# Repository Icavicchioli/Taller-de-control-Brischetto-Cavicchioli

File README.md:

tp1: https://www.overleaf.com/3525453746jbmzhwpqxbmw#78765e

tp2: https://www.overleaf.com/read/swpkgmxtgczf#749885

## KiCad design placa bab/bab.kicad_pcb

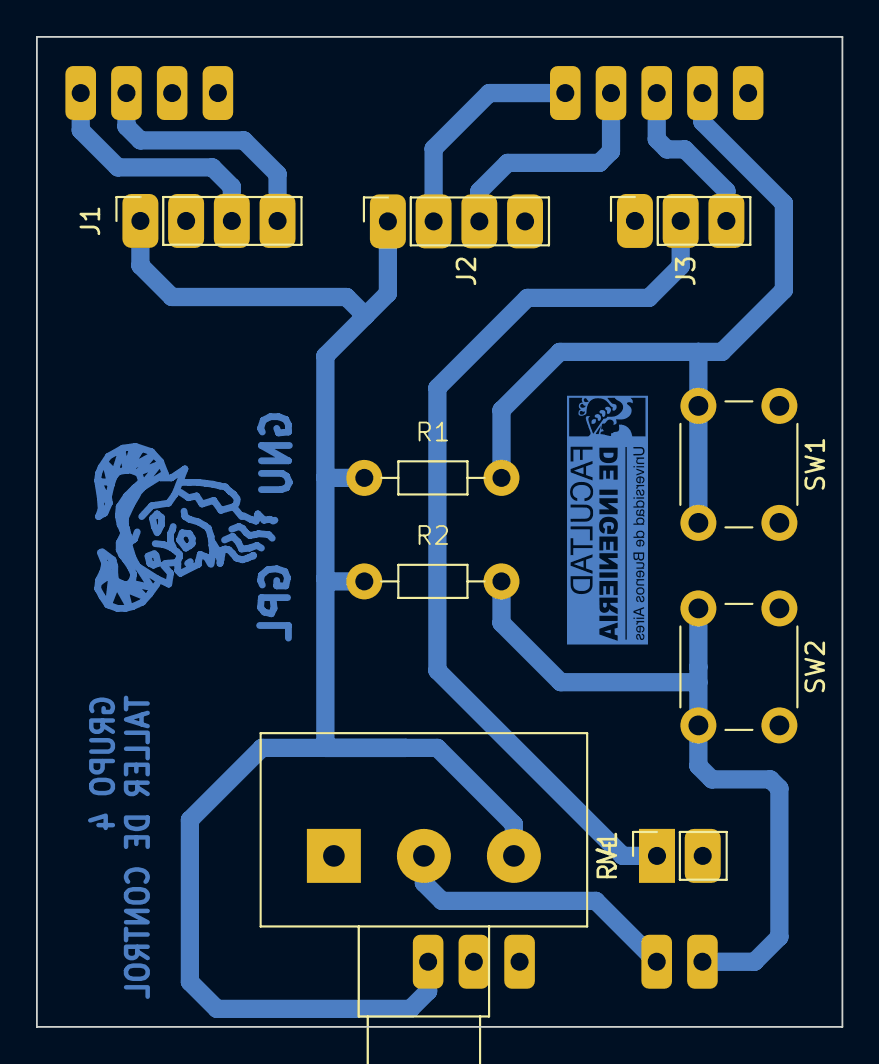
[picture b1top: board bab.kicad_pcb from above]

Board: 2 copper layers, 44.7 x 55.0 mm, 10 parts (1 on the bottom side), 11 nets.

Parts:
A1: Arduino_UNO_R3
J1: IMU; PinSocket_1x04_P2.54mm_Vertical
J2: HC05; PinSocket_1x04_P2.54mm_Vertical
J3: motor; PinSocket_1x03_P2.54mm_Vertical
J4: Alimentacion; PinSocket_1x02_P2.54mm_Vertical
R1, R2: 4K7; Resistencia THT
RV1: R_Potentiometer; Potentiometer_Alps_RK163_Single_Horizontal
SW1, SW2: SW_Push; SW_PUSH_6mm_H5mm

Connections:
+5V: A1.5 (+5V), J1.1, J2.1, R1.1, R2.1, RV1.3
/5v_ext: J3.2, J4.1
BTN1: A1.19 (D4), R1.2, SW1.2
BTN2: A1.10 (A1), R2.2, SW2.2
ECHO: A1.21 (D6), J2.3
GND: A1.6 (GND), A1.7 (GND), A1.29 (GND), J1.2, J2.4, J3.1, J4.2, RV1.1, SW1.1, SW2.1
POT: A1.9 (A0), RV1.2
PWM: A1.20 (D5), J3.3
SCL: A1.32 (SCL/A5), J1.3
SDA: A1.31 (SDA/A4), J1.4
TRIG: A1.22 (D7), J2.2

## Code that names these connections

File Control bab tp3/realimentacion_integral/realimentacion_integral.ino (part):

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#define PI 3.1415

//Definiciones pines
#define ECHO_PIN 6
#define TRIGGER_PIN 7

//Definiciones motor
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#define MOTOR_MIN 800.0
#define MOTOR_CERO 1500.0

#define BTN2 PIN_A1
#define BTN1 4

NewPing sonar(TRIGGER_PIN,ECHO_PIN, 100);
Servo myservo;
Adafruit_MPU6050 mpu;

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  pinMode(A0, INPUT);
  
  //boton de cambio rapido de referencia
  pinMode(BTN2, INPUT);
  pinMode(BTN1, INPUT);

  delay(1000);
}
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
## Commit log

2025-04-08 punto y coma
2025-04-16 pratica de identificaicon de sistmea
2025-04-18 Archivo geogebra imu tp1
    archivo de geogebra que modela el error en la tangente para la IMU en estado estacionadrio
2025-04-23 Correccion practica 4
2025-04-24 funciona
2025-04-24 file matlab funca
2025-04-24 tp entregado
2025-04-30 Control bab
2025-05-06 Practica 6 PID
2025-05-20 Controlador para tp2
2025-05-20 dinamica no lineal rozamiento
2025-05-20 observador
2025-05-20 observador andando?
2025-05-20 Funciona!
2025-05-21 Observador con sesgo funciona
2025-05-25 Graficos
2025-05-25 Plot graficos
2025-05-25 Actualizacion simulink
2025-05-25 simulink
2025-05-26 Agregado de grafico de erro
2025-05-30 observador completo
2025-05-30 Implementacion del observador completo
2025-06-01 ss feedback con feed
2025-06-02 Prueba state feedback
2025-06-03 integral
2025-06-03 Implementacion ssf de integrador
2025-06-03 cambios integrador, no anda
2025-06-03 Integrador
2025-06-06 Correcciones integral
2025-06-06 simu obs con plantano lineal
2025-06-08 pruebas
2025-06-08 simulink osbervador
2025-06-08 Integradores
2025-06-08 curvas observador
2025-06-08 imagenes
2025-06-08 figs de overleaf
2025-06-08 update simulinks
2025-06-10 Graficos medicion planta
2025-06-11 cambios en graficos de señales para feedback sin F
2025-06-12 reorganización y grafs
2025-06-12 cambios varios
2025-06-12 imagenes nuevas
2025-06-13 Actualizacion integral
2025-06-14 sigmoide
2025-06-15 merge
2025-06-15 rename
2025-06-15 sigmoide arduino
2025-06-15 agregé posibilidad de pasar escalones a rampa en simulink de feedthrough
2025-06-16 Mediciones y pruebas
2025-06-16 obs integrador
2025-06-16 Pruebas obs integrador
2025-06-17 metido filtro complementario en mediocioens
2025-06-17 grafs integrador
2025-06-20 simulinks integral
2025-06-26 entrega
2025-06-26 simulinks V2017
